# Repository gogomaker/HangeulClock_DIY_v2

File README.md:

# HangeulClock_DIY_v2
한글시계 v2 - v1을 바탕으로 완전히 새롭게 만드는 v2

## 제작동기: 한글시계 v1을 만들면서 든 한 가지 생각...

'이야 남의 것 배껴서 똑같이 만들었는데 내가 응용해서 만든 것도 하나 있어야지 않겠나...' \
그래서 만들게 된 한글시계 v2 이다. \
-사실 말만 v2이지 상당히 다른 구조를 가지고 있다.

## 이번 프로그래밍에 중요한 사항

특별히 중요한 것은 모든 것을 "함수화"한다는 것이다.

모든 함수는 각자의 기능에 충실하게 작성되어야 하며, 함수 용도 외의 타용도의 코드가 작성되면 안 된다. 반드시 해당 기능만 있어야 한다.

## V2 개선사항(고쳐야 할 점)

PCB에서 flicker 제어선으로 빠지는 곳에 있는 10k옴저항 제거

PCB에 RESET button 추가 및 케이스에 이를 적용

케이스 무게 어떻게든 줄이기(디자인 조정), 전선 꼽히는 부분 조절

외부밝기측정부 재설계(부품이 안 맞으니 조립이 안 됨)

시계의 가장자리 부분으로 빛이 샌다. 이것을 해결할 방법을 찾아야 함.

회로설계에서 버튼핀 재배열 좀 하자(어째서 모드버튼만 2번인가)

아두이노 내부의 전체 순서를 결정하는 time 변수는 이름을 internal_millis 내지는 '내부의 시간기준'이란 뜻을 가질 수 있는 이름으로 변경하기

한글시계 온습도 표시 시에 온도 및 습도(단위)는 네오픽셀 색깔을 다르게 하자.\
색깔이 같으면 숫자 읽을 때 햇갈릴 수도 있을 듯

스위치 디바운싱을 소프트웨어로 처리하지말고 하드웨어로 처리하자. 그럼 얼마나 편하겠니...

## 구현해야하는 기능
버튼을 일정 시간(1200ms)이상 누르고 있으면, 자동으로 길게 누른 것으로 인식해서 작동하는 것. 이 기능이 제대로 작동하지 않음.

## 제작시 참고사항

v1과 달라진 점:

1. 중앙 flicker 추가 - 3번 핀 아날로그 출력 연결

2. 온습도 센서 추가    - 8번 핀 디지털 연결

3. 조도센서 추가     - A1 핀 아날로그 입력 연결

4. 부저 추가 (알람)  - 7번 핀 디지털 연결

5. 각종 버튼 추가    - 각 기능 구현

## 기능별 설명

네오픽셀은 기존의 무지개 색상 및 WarmLED를 추가하였고 이걸 따로 조합해야함

이번 버전에서는 Warm White 기본, 쿨화이트, 무지개 순으로 색깔 진행

~~랜덤의 경우 더 많은(30색)의 색상에서 랜덤으로 추출 가능하도록 설정~~

---

플리커(중앙에 깜빡이는 놈)는 1초마다 켜젔다 꺼졌다를 반복함

타임라인 상으로 보자면

0.0 --- 1.0 --- 2.0 --- 3.0 --- 4.0 s\
O N --- OFF --- O N --- OFF --- O N ... \
이런 형태를 취함

그리고, 이렇게 ON OFF 가 바뀌는 과졍에서 
조금 부드럽게, 그러나 탄력있게 바뀌도록 설계 \
마치 모션 그래픽처럼 \
+탄력있는 건 매우 어려움 \
+플리커는 모든 기능에서 깜박인다, 2초 간격

---

조도센서는\
밝기 조정 모드에서 밝기를 외부 조도에 맞게 
제어하는 모드를 넣음으로써 구현

--------------------------------

온습도 센서는

시계 전면의 버튼을 통하여 시계 - 온습도 표시 모드 변경함\
이 떄, 온도 또는 습도를 2자리 7세그먼트로 보여줌\
ex) *은 LED 점등, .은 LED 소등

    * * *  * * *

    . . *  * . *

    * * *  . . *

    * . .  . . *

    * * *  . . *

    x . .  . . -

    (-는 온습도  LED입니다)

센서는 2초에 1회 업데이트 되며 
평상시에는 업데이트 하지 않다가 
온습도 모드 진입시에 온습도 데이터를 업데이트 하여 표시

--------------------------------

알람 기능은

알람 설정 버튼을 길게 누름으로서 알람 설정 모드로 진입 가능\
알람은 시간 설정하는 방법과 동일하게 설정이 가능하며

알람 설정 버튼을 짧게 누르면 2~5초 동안 알람이 켜져있는지 꺼져있는지가

화면에 O 또는 X 로 나타나게 됨

기능 구현은

가능하다면 DS3231의 내부 알람 기능을 활용하면 좋겠지만

안 된다면 아두이노에서 코드로 작성하는 것으로 함.

--------------------------------

버튼별 기능은

- 시계 전면의 모드 전환 버튼: 모드 전환 역할

   이 버튼은 눌렀다가 땔 때 시간에 관계없이 모드만 바꿔줌.

- 시계 측면 위의 LED 버튼: LED관련 제어 역할

   이 버튼은 짧게 누르면 밝기 변화 길게 누르면 색상이 변화함.

   색상 변화는 네오픽셀 항목 참조.

- 시계 측면 둘째 시간 버튼: 시간을 수정하는 역할

   이 버튼은 처음에 짧게 누르면 반응 없음 길게 누르면 시간 수정 모드로 젼환함.

   시간 수정모드에 진입하게 되면 모든 시간을 표시하는 LED가 깜박임

   이후, 시간 버튼을 짧게 누르면 시단위 1씩 추가 알람 버튼을 짧게 누르면 분단위 1씩 추가된다.

   시간 버튼을 다시 길게 누르면 시간 수정 모드는 종료됨.

- 시계 측면 셋째 알람 버튼: 알람을 설정하는 버튼

   이 버튼은 처음에 짧게 누르면 알람이 활셩화 되어 있는지 아닌지 표시함 \
   시간 버튼과 알람 버튼을 같이 누르게 된다면(오차 20ms이내) 알람을 활성화&비활성화함 \
   이 때 가능하다면 \
    알람이 활성화 될 때는 X가 사라지며 O가 나타나고 \
    알람이 비활성화 될 때는 O가 사라지며 X가 나타나도록 한다.

   처음에 길게 누르면 알람 설정을 하게 된다. \
   이후, 시간 버튼을 짧게 누르면 알람 시단위 1씩 추가 \
   알람 버튼을 짧게 누르면 알람 분단위 1씩 추가된다.\
   알람 버튼을 길게 누른다면 O가 나타나고, 알람은 활성화 된 상태로 알람 설정 모드는 종료됨.

   + 시간 변경 시에는 쉼표가 파란색으로, 알람 변경시에는 쉼표가 녹색으로 점등된다.

## 제작일기
사실 깃헙 readme를 작성하면서 뭘 적아야 될지 모르겠어서 그냥 일기나 적으려 한다.

2021-03 어느 날: 한글시계 v2에 대한 소망과 희망을 가지고 대략적인 디자인 및 기능들을 일주일에 걸쳐 구상한다.

2021-05-29: 한글시계 v2 디자인 착수. 앞판 디자인 완료. 

2021-05-30: 한글시계 v2 의 기본적인 디자인 완료. 

2021-06-07: 깃헙 레포지토리 생성.

2021-06-23: 오랜만에 이 프로젝트를 건드렸다.
지난 2주간 무드등 한글시계 작업한다고 어찌나 바빴던지...
여튼 오늘은, 프로젝트의 실제 파일들을 복사하고, 깃 레포지지토리와 연동시켰다.

2021-08-31: 진짜 오랜만에 일지를 쓴다.
그동안 무드등 한글시계 PCB 작업하느랴 이것저것 만지느랴 바빴다.
그러나 지난 2주 동안, 디자인 및 PCB작업을 모두 완료하였으며, 다음주 중으로 모든 부품과
PCB가 온다.
이제 납땜을 하고 프로그램을 올리면 끝이 난다.
추석 전으로 마무리 하려는데 가능할련지...

2021-09-02: 남는 건 기록밖에 없다...
오늘은 DHT센서 라이브러리를 추가하고, 사용하는 핀을 상수로 지정하였으며, 
모든 기능에 대해 상당히 구체적으로 기술하였다.
위에 보는 바와 같이 말이다.
그리고, 변수명은 아직 못 바꿨다. 그리고 새로운 변수도 추가를 못했다.
내일 흐름을 짜면서 변수들도 필요한 것들 추가하고, 코드를 재정비 해야겠다.

2021-09-08: 간만에 리드미 적는다. 
이번주 토요일에 온라인 발표를 하기에 정신없이 발표 준비중이다.
함꼐 더불어, 코드와 모든 것을 열심히 하고 있다. 
어제 알리에서 SK6812LED를 잘못 보내준 것을 알고...ㅜ.ㅜ 
직구는 언제나 조심해야 하는 것 같다.
오늘은 정신없이 버튼 함수를 뜯어고치는 중이다.

2021-09-09: 이번주는 한글시계로 달리는 주간인가보다. 
오늘은 코드 수정을 정말 열심히 했다. 
v1의 유산을 모두 청산하고, 본격적인 v2 코드의 모습을 잡아가기 시작했다. 
기존에, 나의 기억력으로 숫자로만 지정한 것들도 모두 상수로 전환하고, 
변수 이름의 통일성 없는 것도 모두 새롭게 이름을 바꾸었으며, 
배열을 사용할 수 있는 것은 배열을 사용하였고, 
변수들을 카테고리 별로 정리, 각각 주석을 적었다. 
또한, h파일의 어수선함도 정리하였다.

2021-09-11: 오늘은 영메이커 놀이데이에서 한글시계 관련 발표를 하였고, 
한글시계 PCB의 문제점 중에서 스케치를 바꿔야 하는 작업 빛 푼프린트 수정 작업을 완료하였다..
내일은 PCB아트웤만 끝내면 된ㄷr...

2021-09-15: 그저께부터 3일간 PCB의 문제를 해결하고, 각 부품에 대한 호환성 및 기타 
모든 것을 비교한 결과, 현재로서 완벽하다고 판단되는 PCB를 주문하였다.
이제, 코드에 전력을 기한 다음, 다른 모양의 시계도... ㅎ.ㅎ

2021-10-18: 거의 한 달이 지났다... 
우선, LED는 불량이 와서 문제가 생겼고, 국내에서 구해야 할 것 같다. 
코드의 경우는 지난번의 기억을 더듬어서 마저 작업하던 cpp파일을 이어 수정하였다.
현재, updateHour까지 편집을 완료하였다. 다음부터는 updateMin 함수 편집을 시작하면 된다.

2021-11-15: 또 한 달이 지나서야 리드미를 쓴다. 
그제, 어제, 오늘동안 updateHour, updateMin 수정완료하였다(if->case). 
또한, 변수들을 전부 확인 완료하였다. (더 이상 수정할 변수 없음)
이젠 버튼 함수와 새로운 기능들을 추가해야지...

2021-11-22: 무슨 한글시계 개발을 일주일 간격으로 하는 것 같다...ㅋㅋ 
도대체 이게 무슨 일인지.... 

2022-01-06: 새로운 한 해가 밝았다. 
지난 6일동안 열심히 납땜하고 삽질한 결과, 하드웨어는 성공적으로 완성하였다. 
어제오늘로 나눠 테스트 한 각 부품들의 상태도 최고. 
이제 이 위에서 돌아갈 코드만 짜면 끝난다...

2022-01-09: 벌써 일지 작성한지 3일이 지났네... 
깃헙을 보면 알겠지만, 지난 3일동안 절대 논 것이 아니라 너무 빡세게 코딩 작업을 해서 일지를 안 쓴거다(까먹은 거 안 비밀). 
여튼간에, 오늘까지의 작업을 대략 정리하자면

1. 보기 힘들었던 변수 상태들 싹다 정리
2. 이해 안 갔던 변수 및 함수들 전부 주석 달음
3. 안 쓰는 과거의 코드 다 지움
4. if문들 대거 정리
5. 오늘 새벽 작업 포함 알람 기능까지 작성 완료.

오늘 저녁까지(작성당시 새벽) 프로그래밍 작업 완료하면, 코드 종이에 그려 보면서 오류 있는지 없는지 체크, 논리상 오류나는 부분 없으면 바로 한글시계에 업로딩 해서 실제 테스트를 진행해 본다.

2024-04-27: 이 프로젝트를 마무리한지도 어느덧 1년이 지났다. 대학교 오고 나서 시간이 나기도 하고, 다시 제대로 살려보고 싶어서 코드에 손 대보게 되었다. 진짜로 살려보자. 이제는 나도 능력이 성장했으니...

2024-05-03: 다른 프로젝트로 바쁜 와중에, 이것까지 하려니 정신이 없다. 그래도 내가 하고 싶어서 하는 거다 보니 열정이 난다. 오늘은 코드를 정리하고, 나도 모르게 꼬여 있었던 깃 브랜치를 정리하였다. 

2024-05-04: 오늘도 제법 많은 코드를 정리했다. 브랜치를 하나 별도로 만들어서, 코드를 전체적으로 수정 중에 있다. 

2024-05-06: 새벽에 코드작성하면서 일지를 적어본다. 이제 거의 모든 코드를 다 작성했다. 이제는 실전만 남았다. 과연 수정한 코드가 제대로 작동할지 정말로 궁금하다.

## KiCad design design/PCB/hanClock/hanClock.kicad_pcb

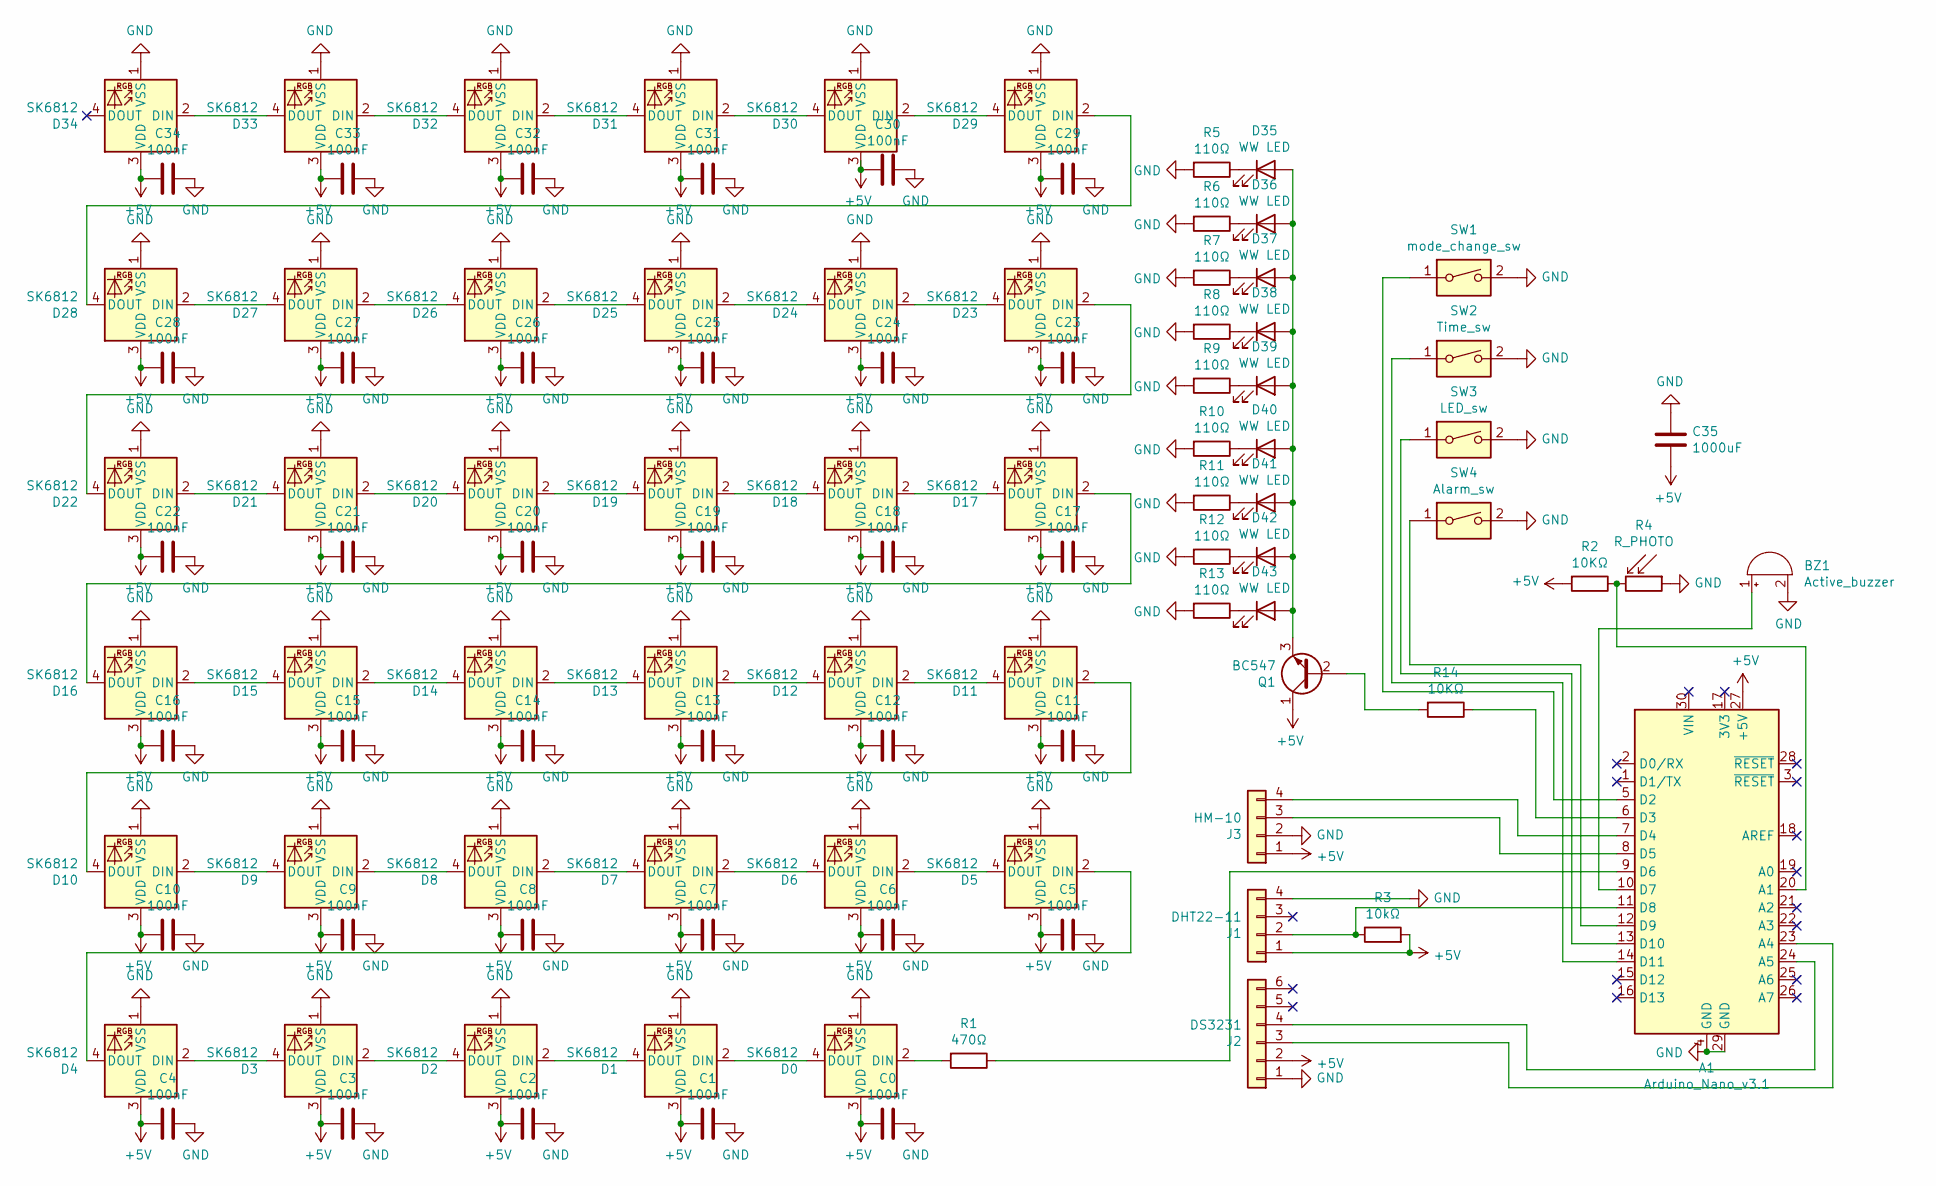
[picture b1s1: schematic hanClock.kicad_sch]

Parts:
A1: Arduino_Nano_v3.1; Arduino_Nano
BZ1: Active_buzzer; buzzer
C0, C1, C2, C3, C4, C5, C6, C7, C8, C9, C10, C11, C12, C13, C14, C15, C16, C17, C18, C19, C20, C21, C22, C23, C24, C25, C26, C27, C28, C29, C30, C31, C32, C33, C34: 100nF; C_1206_3216Metric_Pad1.33x1.80mm_HandSolder
C35: 1000uF; C_K14
D0, D1, D2, D3, D4, D5, D6, D7, D8, D9, D10, D11, D12, D13, D14, D15, D16, D17, D18, D19, D20, D21, D22, D23, D24, D25, D26, D27, D28, D29, D30, D31, D32, D33, D34: SK6812; LED_SK6812_PLCC4_5.0x5.0mm_P3.2mm
D35, D36, D37, D38, D39, D40, D41, D42, D43: WW LED; LED_1206_3216Metric_Pad1.42x1.75mm_HandSolder
J1: DHT22-11; PinSocket_1x04_P2.54mm_Vertical
J2: DS3231; PinSocket_1x06_P2.54mm_Vertical
J3: HM-10; PinSocket_1x04_P2.54mm_Vertical
Q1: BC547
R1: 470Ω; R_Axial_DIN0207_L6.3mm_D2.5mm_P10.16mm_Horizontal
R2, R14: 10KΩ; R_Axial_DIN0207_L6.3mm_D2.5mm_P10.16mm_Horizontal
R3: 10kΩ; R_Axial_DIN0207_L6.3mm_D2.5mm_P10.16mm_Horizontal
R4: R_PHOTO; R_Axial_DIN0204_L3.6mm_D1.6mm_P2.54mm_Vertical
R5, R6, R7, R8, R9, R10, R11, R12, R13: 110Ω; R_1206_3216Metric_Pad1.30x1.75mm_HandSolder
SW1: mode_change_sw; SMDbutton
SW2: Time_sw; KLT_SW
SW3: LED_sw; KLT_SW
SW4: Alarm_sw; KLT_SW

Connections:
+5V: A1.27 (+5V), C0.2, C1.2, C2.2, C3.2, C4.2, C5.2, C6.2, C7.2, C8.2, C9.2, C10.2, C11.2, C12.2, C13.2, C14.2, C15.2, C16.2, C17.2, C18.2, C19.2, C20.2, C21.2, C22.2, C23.2, C24.2, C25.2, C26.2, C27.2, C28.2, C29.2, C30.2, C31.2, C32.2, C33.2, C34.2, C35.2, D0.3 (VDD), D1.3 (VDD), D2.3 (VDD), D3.3 (VDD), D4.3 (VDD), D5.3 (VDD), D6.3 (VDD), D7.3 (VDD), D8.3 (VDD), D9.3 (VDD), D10.3 (VDD), D11.3 (VDD), D12.3 (VDD), D13.3 (VDD), D14.3 (VDD), D15.3 (VDD), D16.3 (VDD), D17.3 (VDD), D18.3 (VDD), D19.3 (VDD), D20.3 (VDD), D21.3 (VDD), D22.3 (VDD), D23.3 (VDD), D24.3 (VDD), D25.3 (VDD), D26.3 (VDD), D27.3 (VDD), D28.3 (VDD), D29.3 (VDD), D30.3 (VDD), D31.3 (VDD), D32.3 (VDD), D33.3 (VDD), D34.3 (VDD), J1.1, J2.2, J3.1, Q1.1 (C), R2.2, R3.2
GND: A1.4 (GND), A1.29 (GND), BZ1.2 (+), C0.1, C1.1, C2.1, C3.1, C4.1, C5.1, C6.1, C7.1, C8.1, C9.1, C10.1, C11.1, C12.1, C13.1, C14.1, C15.1, C16.1, C17.1, C18.1, C19.1, C20.1, C21.1, C22.1, C23.1, C24.1, C25.1, C26.1, C27.1, C28.1, C29.1, C30.1, C31.1, C32.1, C33.1, C34.1, C35.1, D0.1 (VSS), D1.1 (VSS), D2.1 (VSS), D3.1 (VSS), D4.1 (VSS), D5.1 (VSS), D6.1 (VSS), D7.1 (VSS), D8.1 (VSS), D9.1 (VSS), D10.1 (VSS), D11.1 (VSS), D12.1 (VSS), D13.1 (VSS), D14.1 (VSS), D15.1 (VSS), D16.1 (VSS), D17.1 (VSS), D18.1 (VSS), D19.1 (VSS), D20.1 (VSS), D21.1 (VSS), D22.1 (VSS), D23.1 (VSS), D24.1 (VSS), D25.1 (VSS), D26.1 (VSS), D27.1 (VSS), D28.1 (VSS), D29.1 (VSS), D30.1 (VSS), D31.1 (VSS), D32.1 (VSS), D33.1 (VSS), D34.1 (VSS), J1.4, J2.1, J3.2, R4.1, R5.2, R6.2, R7.2, R8.2, R9.2, R10.2, R11.2, R12.2, R13.2, SW1.2, SW2.2, SW3.2, SW4.2
unnamed: A1.5 (D2), SW1.1
unnamed: A1.6 (D3), R14.1
unnamed: A1.7 (D4), J3.4
unnamed: A1.8 (D5), J3.3
unnamed: A1.9 (D6), R1.1
unnamed: A1.10 (D7), BZ1.1 (-)
unnamed: A1.11 (D8), J1.2, R3.1
unnamed: A1.12 (D9), SW4.1
unnamed: A1.13 (D10), SW3.1
unnamed: A1.14 (D11), SW2.1
unnamed: A1.20 (A1), R2.1, R4.2
unnamed: A1.23 (A4), J2.3
unnamed: A1.24 (A5), J2.4
unnamed: D0.2 (DIN), R1.2
unnamed: D0.4 (DOUT), D1.2 (DIN)
unnamed: D1.4 (DOUT), D2.2 (DIN)
unnamed: D2.4 (DOUT), D3.2 (DIN)
unnamed: D3.4 (DOUT), D4.2 (DIN)
unnamed: D4.4 (DOUT), D5.2 (DIN)
unnamed: D5.4 (DOUT), D6.2 (DIN)
unnamed: D6.4 (DOUT), D7.2 (DIN)
unnamed: D7.4 (DOUT), D8.2 (DIN)
unnamed: D8.4 (DOUT), D9.2 (DIN)
unnamed: D9.4 (DOUT), D10.2 (DIN)
unnamed: D10.4 (DOUT), D11.2 (DIN)
unnamed: D11.4 (DOUT), D12.2 (DIN)
unnamed: D12.4 (DOUT), D13.2 (DIN)
unnamed: D13.4 (DOUT), D14.2 (DIN)
unnamed: D14.4 (DOUT), D15.2 (DIN)
unnamed: D15.4 (DOUT), D16.2 (DIN)
unnamed: D16.4 (DOUT), D17.2 (DIN)
unnamed: D17.4 (DOUT), D18.2 (DIN)
unnamed: D18.4 (DOUT), D19.2 (DIN)
unnamed: D19.4 (DOUT), D20.2 (DIN)
unnamed: D20.4 (DOUT), D21.2 (DIN)
unnamed: D21.4 (DOUT), D22.2 (DIN)
unnamed: D22.4 (DOUT), D23.2 (DIN)
unnamed: D23.4 (DOUT), D24.2 (DIN)
unnamed: D24.4 (DOUT), D25.2 (DIN)
unnamed: D25.4 (DOUT), D26.2 (DIN)
unnamed: D26.4 (DOUT), D27.2 (DIN)
unnamed: D27.4 (DOUT), D28.2 (DIN)
unnamed: D28.4 (DOUT), D29.2 (DIN)
unnamed: D29.4 (DOUT), D30.2 (DIN)
unnamed: D30.4 (DOUT), D31.2 (DIN)
unnamed: D31.4 (DOUT), D32.2 (DIN)
unnamed: D32.4 (DOUT), D33.2 (DIN)
unnamed: D33.4 (DOUT), D34.2 (DIN)
unnamed: D35.1 (K), R5.1
unnamed: D35.2 (A), D36.2 (A), D37.2 (A), D38.2 (A), D39.2 (A), D40.2 (A), D41.2 (A), D42.2 (A), D43.2 (A), Q1.3 (E)
unnamed: D36.1 (K), R6.1
unnamed: D37.1 (K), R7.1
unnamed: D38.1 (K), R8.1
unnamed: D39.1 (K), R9.1
unnamed: D40.1 (K), R10.1
unnamed: D41.1 (K), R11.1
unnamed: D42.1 (K), R12.1
unnamed: D43.1 (K), R13.1
unnamed: Q1.2 (B), R14.2

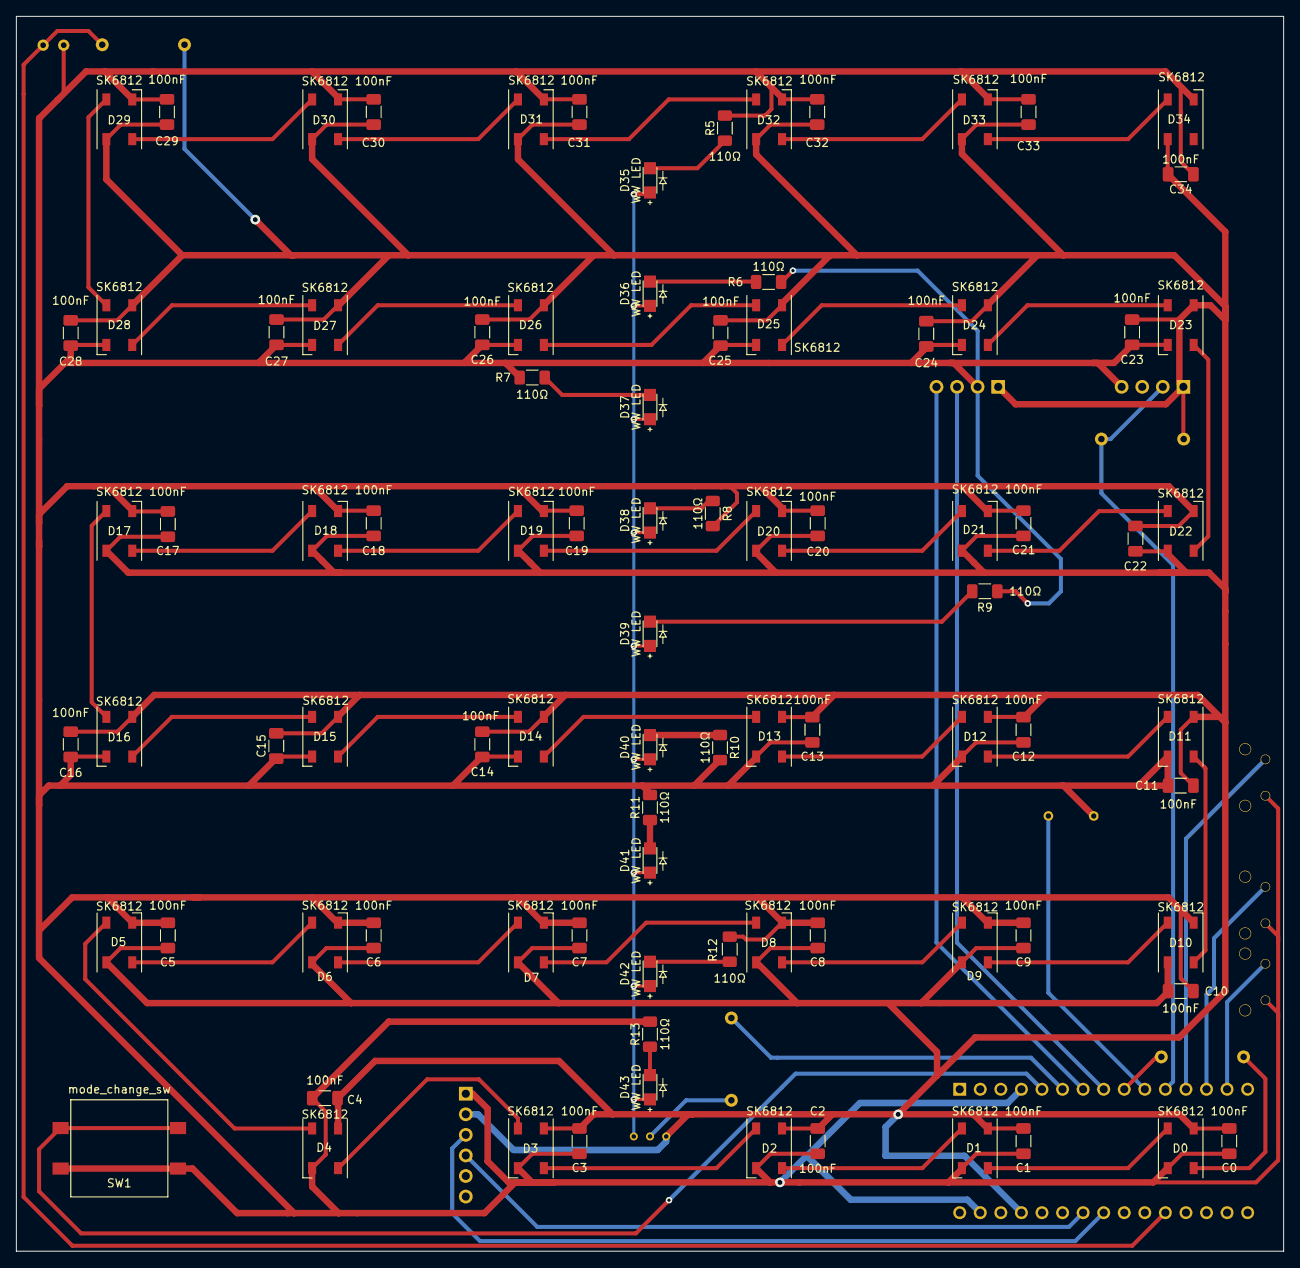
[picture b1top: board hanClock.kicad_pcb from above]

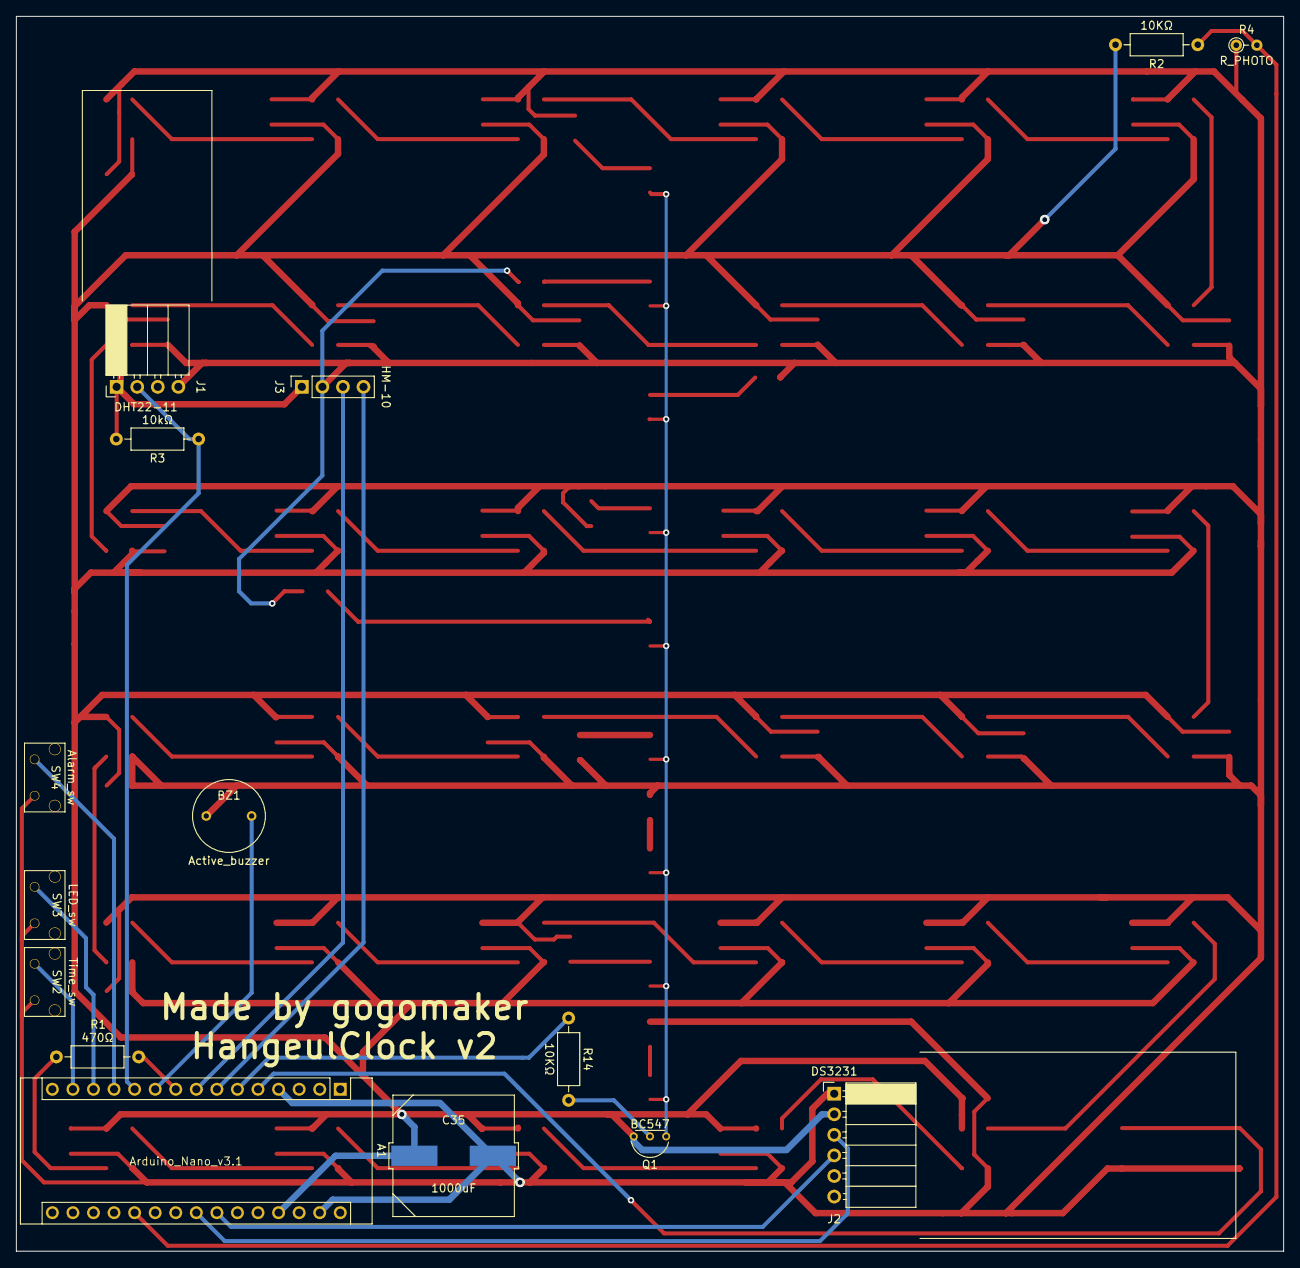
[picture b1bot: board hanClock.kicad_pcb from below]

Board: 2 copper layers, 156.5 x 152.5 mm, 104 parts (15 on the bottom side), 61 nets.

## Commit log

2021-06-23 basic setting 코드의 주석을 수정하고 작업을 할 수 있게 준비하였다.
2021-07-28 create PCB file
2021-08-26 Finished design 커밋을 안 한 한참동안 PCB 다 만들고 외부 디자인도 다 해서 파일을 이렇게 저장했다.
2021-08-31 어지러운 코드를 정리하였다. 도저히 영어로는 뭐라 할지 모르겠어서 한국어로 커밋했다. 제목 그대로 v1에서 배껴와서 각종 환경설정 빛 맞지 않는 변수명들을 모두 수정하고, 더러운 코드들을 모두 보기 좋게 정렬하였다.
2021-09-02 코드는 수정 중 수정 중에 커밋을 한다. 이번 작업에는 상수 추가, 모든 기능에 대한 설명 추가, DHT모듈 임포트 등의 수정사항이 있습니다.
2021-09-08 함수 뜯어고치기 버튼 관련 변수명 정리 및 구조 개선, 함수 수정 중 무언가를 하는 중에 하는 커밋은 좋지 않다 하지만... 잃단 해 본다.
2021-09-09 아직도 코드는 수정 중 현재, 변수명을 드디어 정리했고, v1의 유산인 많은 더러운 코딩 실력도 최대한 정리했다. 그러나 버튼 함수의 if문 깊이는 도저히...ㅜ 여튼, 열심히 수정 중이다.
2021-09-11 PCB디자인 하는 중
2021-09-15 Revise PCB design
2021-10-18 코드작성중
2021-11-15 LED출력코드 수정완료 LED출력하는 주소값들을 모두 수정 완료하였다
2021-11-23 리드미 수정 및 향후 계획 수립
2021-12-09 의사코드 작성 오늘은 의사코드를 아침에 작성해 보았다. 아직 버튼 동작 구현 부분에서 조금은 덜 작성한 부분이 있다. 특히, 알람버튼 코드는 어렵...
2022-01-06 new commit at win11 테스트용 커밋
2022-01-06 과거를 청산하는 프로그램 수정 많은 것을 했다. 전체 코드에 대한 통일성 및 부족한 함수 추가, 코드 정리 완료. 또한, 변수명 재설정 및 상수 재정의 완료, 헤더파일 정리. 버튼 함수 피의 숙청함
2022-01-06 Changed a little parts 우선, 아까전 커밋 때보다 시계구동코드를 좀 적어두었다. 또한, 거의 모든 숫자를 상수화 시켜서 상수에조차 주석을 달았다. 나는야 주석왕... 이제 자야지...zZzZ
2022-01-07 폴더 재구성 및 코드 적는중 우선, 프로젝트의 전체 구성 자체를 재정리했다. 카테고리에 맞게 모든 파일들을 폴더로 넣었다. 또한, 코드에서 시간수정모드 및 알람수정모드의 경우에 대한 코딩을 완료하였다. 다만, 알람모드 기능에 대한 정의가 불확실하여 코드를 짜지 못한 부분도 있다.
2022-01-08 ing_ing_ing
2022-01-08 Finished SW motion code 스위치에 반응하는 모든 코드 작성 완료
2022-02-12 Resync files 컴퓨터 갈아엎으면서 바뀐 파일 등 기타 모든 파일들 일괄 커밋
2022-04-13 updaeting...
2022-05-27 Added_flowchart
2024-04-26 Restart restart
2024-05-03 Sync files 이 커밋은 별다른 건 없고, 두 환경-노트북과 데스크톱-간에 서로 호환이 되는지 확인하는 커밋이다.
2024-05-03 Clean every files
2024-05-05 코드 수정중
2024-05-05 중간에 커밋
2024-05-06 semi-final
2024-05-14 코드 수정중 거의 다 수정해 가는 중이다. 지금은, 코드가 뒤죽박죽이라, 코드를 재정비해야한다.
2024-05-14 RTC version complete
2024-05-14 Make non_RTC Version code
